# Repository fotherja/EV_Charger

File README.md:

# EV_Charger
Arduino Uno Code for EV Charger together with the design files etc

This project is documented in detail here: https://jamesfotherby.com/index-page/electric-vehicle-charger/

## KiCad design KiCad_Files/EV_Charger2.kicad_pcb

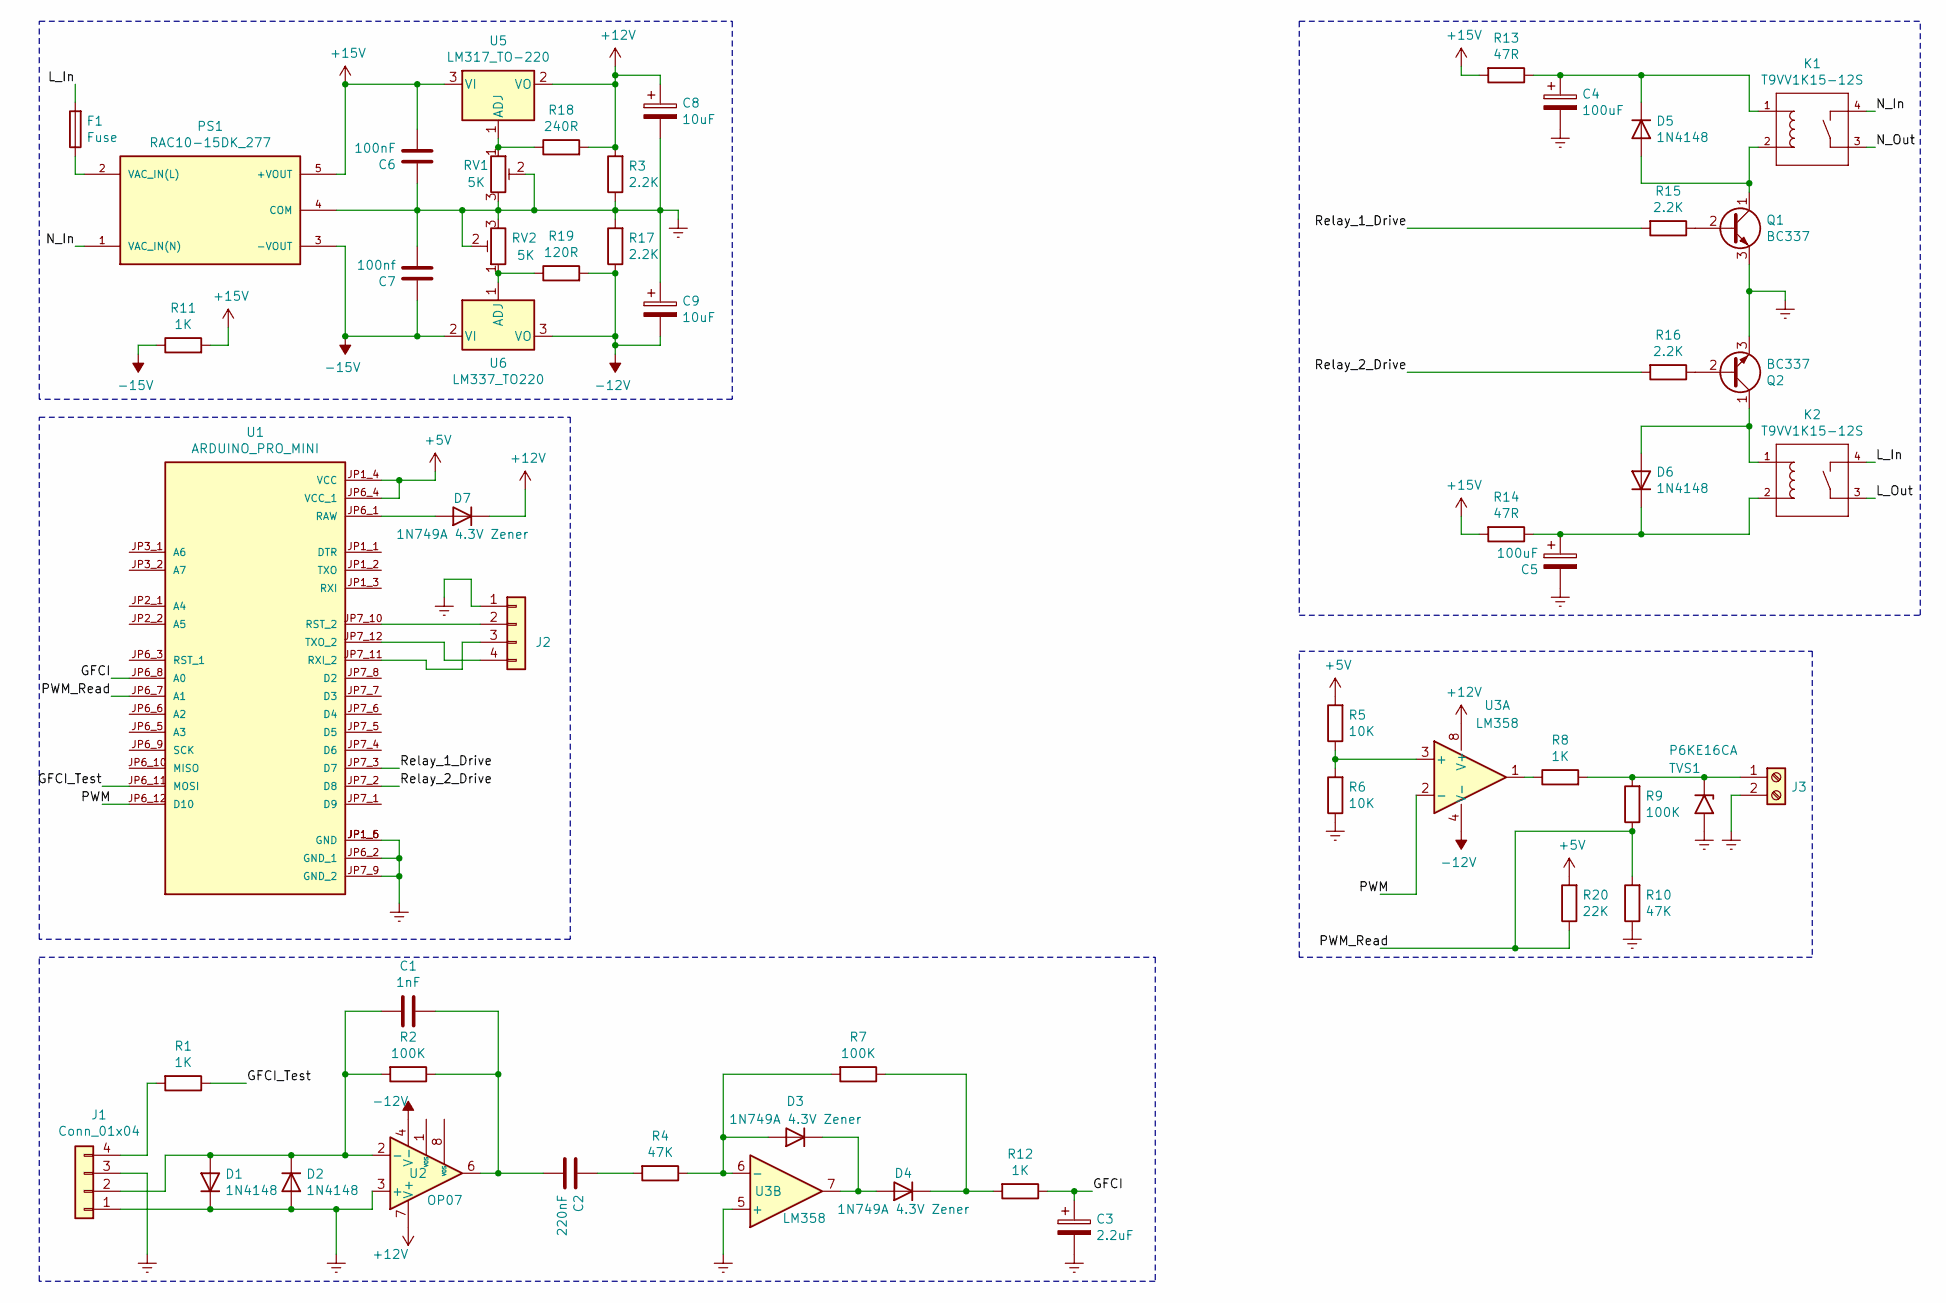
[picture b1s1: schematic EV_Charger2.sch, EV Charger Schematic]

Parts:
C1: 1nF; C_Disc_D3.4mm_W2.1mm_P2.50mm
C2: 220nF; C_Disc_D3.4mm_W2.1mm_P2.50mm
C3: 2.2uF; CP_Radial_D4.0mm_P1.50mm
C4, C5: 100uF; CP_Radial_D5.0mm_P2.50mm
C6: 100nF; C_Disc_D3.4mm_W2.1mm_P2.50mm
C7: 100nf; C_Disc_D3.4mm_W2.1mm_P2.50mm
C8, C9: 10uF; CP_Radial_D5.0mm_P2.50mm
D1, D2, D5, D6: 1N4148; D_DO-35_SOD27_P7.62mm_Horizontal
D3, D4, D7: 1N749A 4.3V Zener; D_DO-35_SOD27_P7.62mm_Horizontal
F1: Fuse; Fuseholder5x20_horiz_open_lateral_Type-II
J1, J2: Conn_01x04; Pin_Header_Straight_1x04_Pitch2.54mm
J3: Screw_Terminal_01x02; Socket_Strip_Straight_1x02_Pitch2.54mm
K1, K2: T9VV1K15-12S; RELAY_T9VV1K15-12S
PS1: RAC10-15DK_277; CONV_RAC10-15DK_277; PARTREV 8/2020
Q1, Q2: BC337; TO-92_Molded_Narrow
R1, R8, R12: 1K; R_Axial_DIN0207_L6.3mm_D2.5mm_P10.16mm_Horizontal
R2, R7, R9: 100K; R_Axial_DIN0207_L6.3mm_D2.5mm_P10.16mm_Horizontal
R3, R15, R16, R17: 2.2K; R_Axial_DIN0207_L6.3mm_D2.5mm_P10.16mm_Horizontal
R4, R10: 47K; R_Axial_DIN0207_L6.3mm_D2.5mm_P10.16mm_Horizontal
R5, R6: 10K; R_Axial_DIN0207_L6.3mm_D2.5mm_P10.16mm_Horizontal
R11: 1K; R_Axial_DIN0309_L9.0mm_D3.2mm_P15.24mm_Horizontal
R13, R14: 47R; R_Axial_DIN0309_L9.0mm_D3.2mm_P15.24mm_Horizontal
R18: 240R; R_Axial_DIN0207_L6.3mm_D2.5mm_P10.16mm_Horizontal
R19: 120R; R_Axial_DIN0207_L6.3mm_D2.5mm_P10.16mm_Horizontal
R20: 22K; R_Axial_DIN0207_L6.3mm_D2.5mm_P10.16mm_Horizontal
RV1, RV2: 5K; Potentiometer_Trimmer_Bourns_PV36W
TVS1: P6KE16CA; D_DO-35_SOD27_P10.16mm_Horizontal
U1: ARDUINO_PRO_MINI; MODULE_ARDUINO_PRO_MINI; PARTREV N/A
U2: OP07; DIP-8_W7.62mm
U3: LM358; DIP794W45P254L959H508Q8
U5: LM317_TO-220; TO-220-3_Vertical
U6: LM337_TO220; TO-220-3_Vertical

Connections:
+5V: R5.2, R20.2, U1.JP1_4 (VCC), U1.JP6_4 (VCC_1)
+12V: C8.1, D7.1 (K), R3.2, R18.2, U2.7 (V+), U3.8 (V+), U5.2 (VO)
+15V: C6.2, PS1.5 (+VOUT), R11.2, R13.2, R14.2, U5.3 (VI)
-12V: C9.2, R17.1, R19.2, U2.4 (V-), U3.4 (V-), U6.3 (VO)
-15V: C7.1, PS1.3 (-VOUT), R11.1, U6.2 (VI)
/GFCI: C3.1, R12.1, U1.JP6_8 (A0)
/GFCI_Test: R1.1, U1.JP6_11 (MOSI)
/L_In: F1.2, K2.4; also elsewhere on the board
/L_Out: K2.3; also elsewhere on the board
/N_In: K1.4, PS1.1 (VAC_IN(N)); also elsewhere on the board
/N_Out: K1.3; also elsewhere on the board
/PWM: U1.JP6_12 (D10), U3.2 (-)
/PWM_Read: R9.1, R10.2, R20.1, U1.JP6_7 (A1)
/Relay_1_Drive: R15.2, U1.JP7_3 (D7)
/Relay_2_Drive: R16.2, U1.JP7_2 (D8)
Earth: C3.2, C4.2, C5.2, C6.1, C7.2, C8.2, C9.1, D1.1 (K), D2.2 (A), J1.1, J1.3, J2.1, J3.2, PS1.4 (COM), Q1.3 (E), Q2.3 (E), R3.1, R6.1, R10.1, R17.2, RV1.2, RV1.3, RV2.2, RV2.3, TVS1.2 (A2), U1.JP1_5 (GND), U1.JP1_6 (GND), U1.JP6_2 (GND_1), U1.JP7_9 (GND_2), U2.3 (+), U3.5 (+); also elsewhere on the board
unnamed: C1.1, C2.2, R2.1, U2.6
unnamed: C1.2, D1.2 (A), D2.1 (K), J1.2, R2.2, U2.2 (-)
unnamed: C2.1, R4.2
unnamed: C4.1, D5.1 (K), K1.1, R13.1
unnamed: C5.1, D6.1 (K), K2.2, R14.1
unnamed: D3.1 (K), D4.2 (A), U3.7
unnamed: D3.2 (A), R4.1, R7.2, U3.6 (-)
unnamed: D4.1 (K), R7.1, R12.2
unnamed: D5.2 (A), K1.2, Q1.1 (C)
unnamed: D6.2 (A), K2.1, Q2.1 (C)
unnamed: D7.2 (A), U1.JP6_1 (RAW)
unnamed: F1.1, PS1.2 (VAC_IN(L))
unnamed: J1.4, R1.2
unnamed: J2.2, U1.JP7_10 (RST_2)
unnamed: J2.3, U1.JP7_11 (RXI_2)
unnamed: J2.4, U1.JP7_12 (TXO_2)
unnamed: J3.1, R8.2, R9.2, TVS1.1 (A1)
unnamed: Q1.2 (B), R15.1
unnamed: Q2.2 (B), R16.1
unnamed: R5.1, R6.2, U3.3 (+)
unnamed: R8.1, U3.1
unnamed: R18.1, RV1.1, U5.1 (ADJ)
unnamed: R19.1, RV2.1, U6.1 (ADJ)

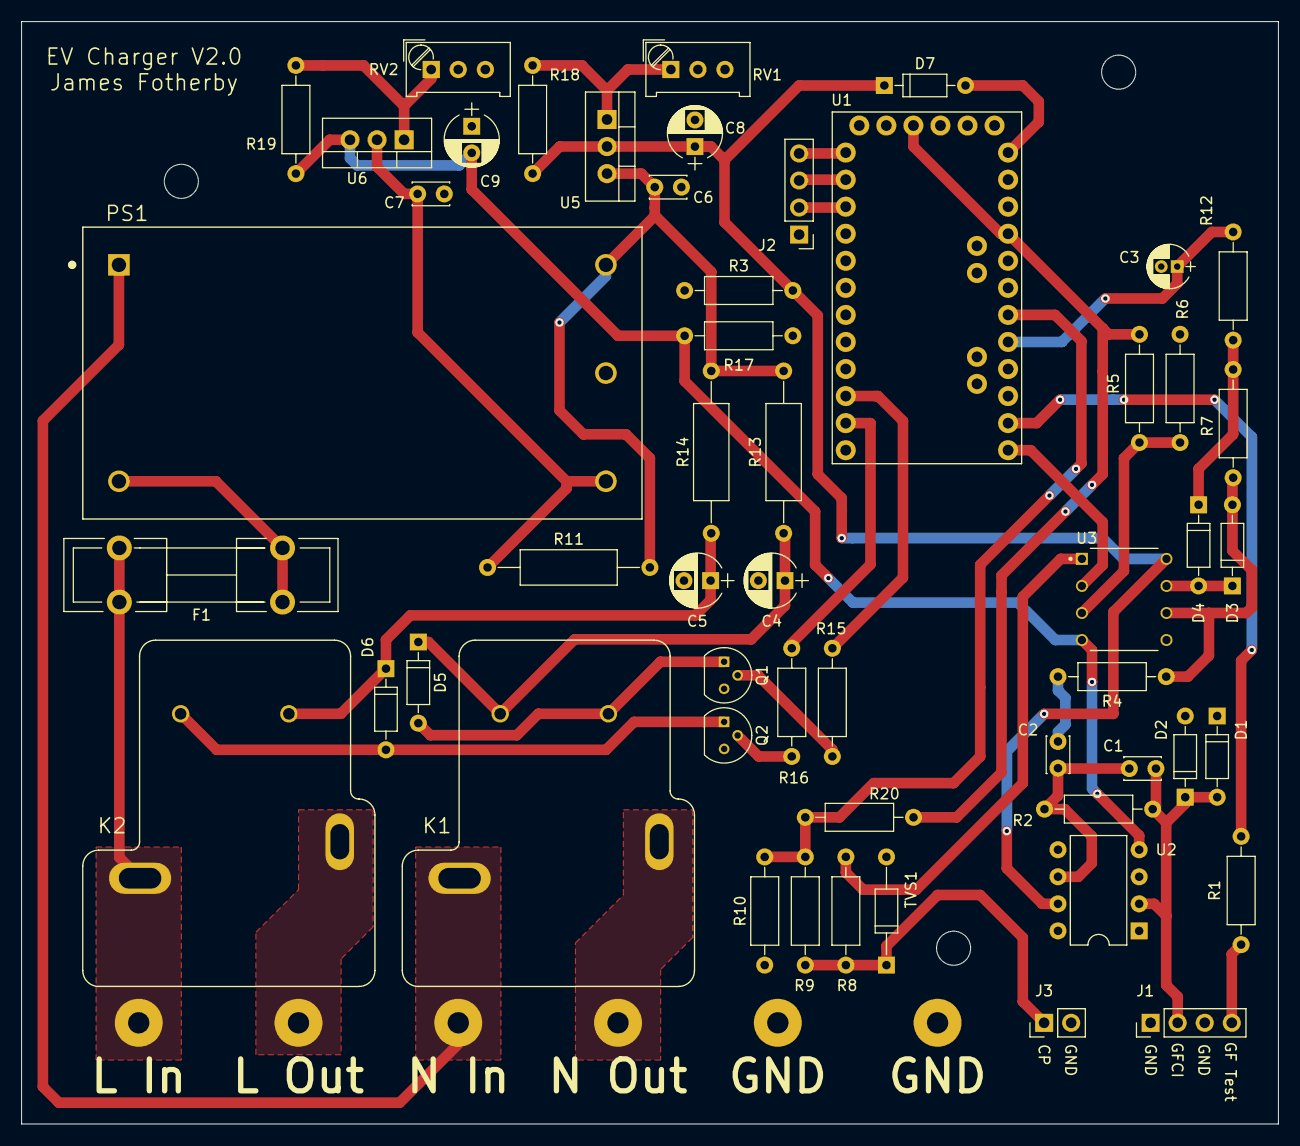
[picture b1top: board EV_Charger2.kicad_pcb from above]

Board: 2 copper layers, 118.0 x 103.5 mm, 59 parts (0 on the bottom side), 39 nets.

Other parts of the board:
GND: SolderWirePad_single_2mmDrill
GND#2: SolderWirePad_single_2mmDrill
L In: SolderWirePad_single_2mmDrill
L Out: SolderWirePad_single_2mmDrill
N In: SolderWirePad_single_2mmDrill
N Out: SolderWirePad_single_2mmDrill

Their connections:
/L_In: L In.1; also elsewhere on the board
/L_Out: L Out.1; also elsewhere on the board
/N_In: N In.1; also elsewhere on the board
/N_Out: N Out.1; also elsewhere on the board
Earth: GND.1, GND#2.1; also elsewhere on the board

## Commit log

2022-04-19 Working 1st Upload
    - Needs better fault management - current code simply makes the unit safe and goes into and infinite while loop
2022-05-22 WDT and bug fix
    Added WDT
    Fixed a bug identified by bosston88 in the Timer interrupts where the ADC channel wasn't being alternated properly
    Changed required successive trivial faults from 100 to 10
2024-01-11 Reduced GFCI sensitivity
    A Zoe ZE50 was occasionally tripping out the GFCI. I think it was set too sensitive so I have increased the ADC threshold for a trip
    It now takes around 40ms to detect a 25mA ground current which is still fine.
    All working well otherwise and has been in constant use for the past couple years
